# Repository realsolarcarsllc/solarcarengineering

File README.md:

# Solar Car Engineering Support Package

This is a combined repository for most RSC boards.

We are packaging everything together for easier downloads. 
Look for the green "code" menu above. 
Open it and select the "Download Zip" option.

# Engineering Info
- Contactors and Battery Connections (SCE 01)
- Charging EVs from Supercapacitors (they don't hold enough energy)

# Boards
- pcdb2105 - 36v to 400v dc-dc converter with MPPT, aux buck converter, contactor control, coil economizer, dual CAN, failsafe CAN bridge, real time clock
- bci2103 - 40 pin connector to wire interface, with holes for pass-through diodes

© 2022 Real Solar Cars, LLC  
PO Box 9372   
Albuquerque, NM 87119-9372  
USA

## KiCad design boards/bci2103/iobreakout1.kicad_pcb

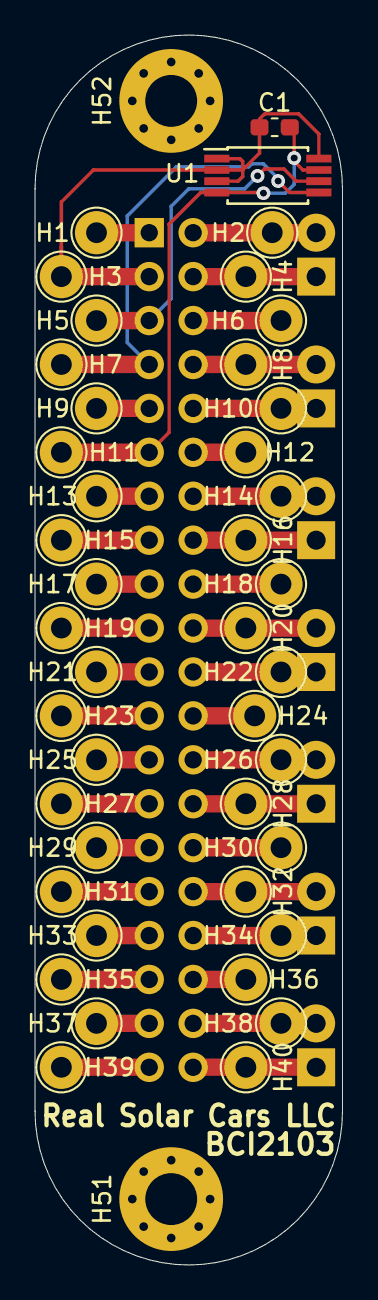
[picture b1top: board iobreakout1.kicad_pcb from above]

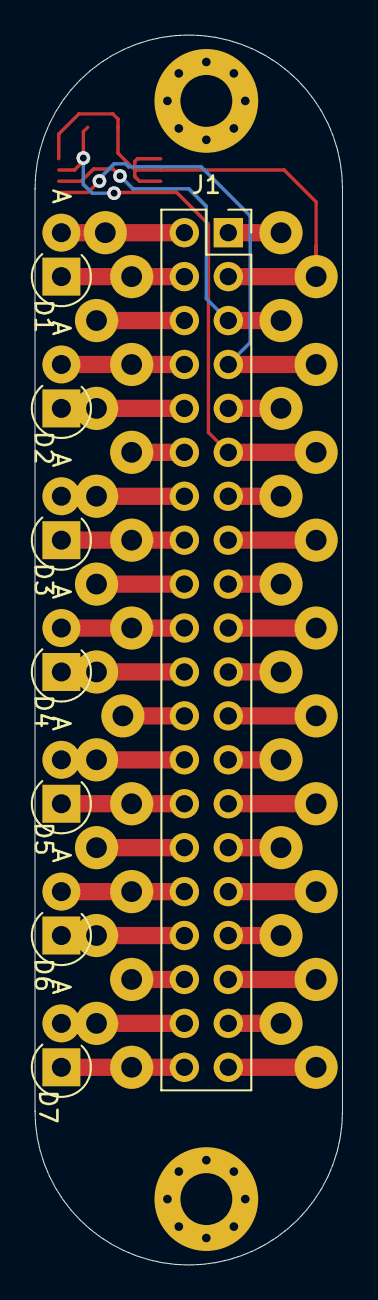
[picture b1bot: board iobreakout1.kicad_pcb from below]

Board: 2 copper layers, 17.8 x 71.1 mm, 52 parts (8 on the bottom side), 40 nets.

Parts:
C1: .1uF; C_0603_1608Metric_Pad1.05x0.95mm_HandSolder
D1, D2, D3, D4, D5, D6, D7: 1N5819; D_DO-41_SOD81_P2.54mm_Vertical_AnodeUp
H1, H2, H3, H4, H5, H6, H7, H8, H9, H10, H11, H12, H13, H14, H15, H16, H17, H18, H19, H20, H21, H22, H23, H24, H25, H26, H27, H28, H29, H30, H31, H32, H33, H34, H35, H36, H37, H38, H39, H40: MountingHole_Pad; TestPoint_THTPad_D2.5mm_Drill1.2mm
H51, H52: MountingHole_Pad; MountingHole_3mm_Pad_Via
J1: Conn_02x20_Odd_Even; PinSocket_2x20_P2.54mm_Vertical
U1: 24LC512; TSSOP-8_4.4x3mm_P0.65mm

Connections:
GND: C1.2, H11.1, J1.11, U1.4, U1.7
unnamed: D1.1, H4.1, J1.4
unnamed: D1.2, H2.1, J1.2
unnamed: D2.1, H10.1, J1.10
unnamed: D2.2, H8.1, J1.8
unnamed: D3.1, H16.1, J1.16
unnamed: D3.2, H14.1, J1.14
unnamed: D4.1, H22.1, J1.22
unnamed: D4.2, H20.1, J1.20
unnamed: D5.1, H28.1, J1.28
unnamed: D5.2, H26.1, J1.26
unnamed: D6.1, H34.1, J1.34
unnamed: D6.2, H32.1, J1.32
unnamed: D7.1, H40.1, J1.40
unnamed: D7.2, H38.1, J1.38
unnamed: H1.1, J1.1
unnamed: H6.1, J1.6
unnamed: H9.1, J1.9
unnamed: H12.1, J1.12
unnamed: H13.1, J1.13
unnamed: H15.1, J1.15
unnamed: H17.1, J1.17
unnamed: H18.1, J1.18
unnamed: H19.1, J1.19
unnamed: H21.1, J1.21
unnamed: H23.1, J1.23
unnamed: H24.1, J1.24
unnamed: H25.1, J1.25
unnamed: H27.1, J1.27
unnamed: H29.1, J1.29
unnamed: H30.1, J1.30
unnamed: H31.1, J1.31
unnamed: H33.1, J1.33
unnamed: H35.1, J1.35
unnamed: H36.1, J1.36
unnamed: H37.1, J1.37
unnamed: H39.1, J1.39
P23SCL: H5.1, J1.5, U1.6
P24SDA: H7.1, J1.7, U1.5
V3.3_DIGITAL: C1.1, H3.1, J1.3, U1.1, U1.2, U1.3, U1.8

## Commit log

2021-10-12 created README
2021-10-12 Add pcdb2105
2021-10-12 add bci2103
2021-10-12 separate dirs for pcb and software
2021-10-12 Add order form
2021-10-12 Some engineering worksheets for contactors and supercapacitors
2021-10-12 breakout board schematic in PDF
2021-10-12 Where to get the compiler
2021-10-12 preview link for BOM
2021-10-12 Schematic preview link
2021-10-14 More accurate input voltage sensor using DAC for calibration
2022-04-27 policy compliance
2022-05-02 Linguist config
2022-05-02 We do not generally prohibit use of GitHub for advertising, but we won't tell you what files flagged your repository.
2022-05-02 Removed ibom.html
2022-06-16 Standalone test program
2022-09-10 Basic relay control functions for DRV89xx
2022-09-10 Add tof to PLC library
2022-09-10 ADC libary to support calibration using multiplexer
2022-09-11 Volt G1 minimum viable product
2022-10-23 Chevy Volt 2014 charge while parked basic
